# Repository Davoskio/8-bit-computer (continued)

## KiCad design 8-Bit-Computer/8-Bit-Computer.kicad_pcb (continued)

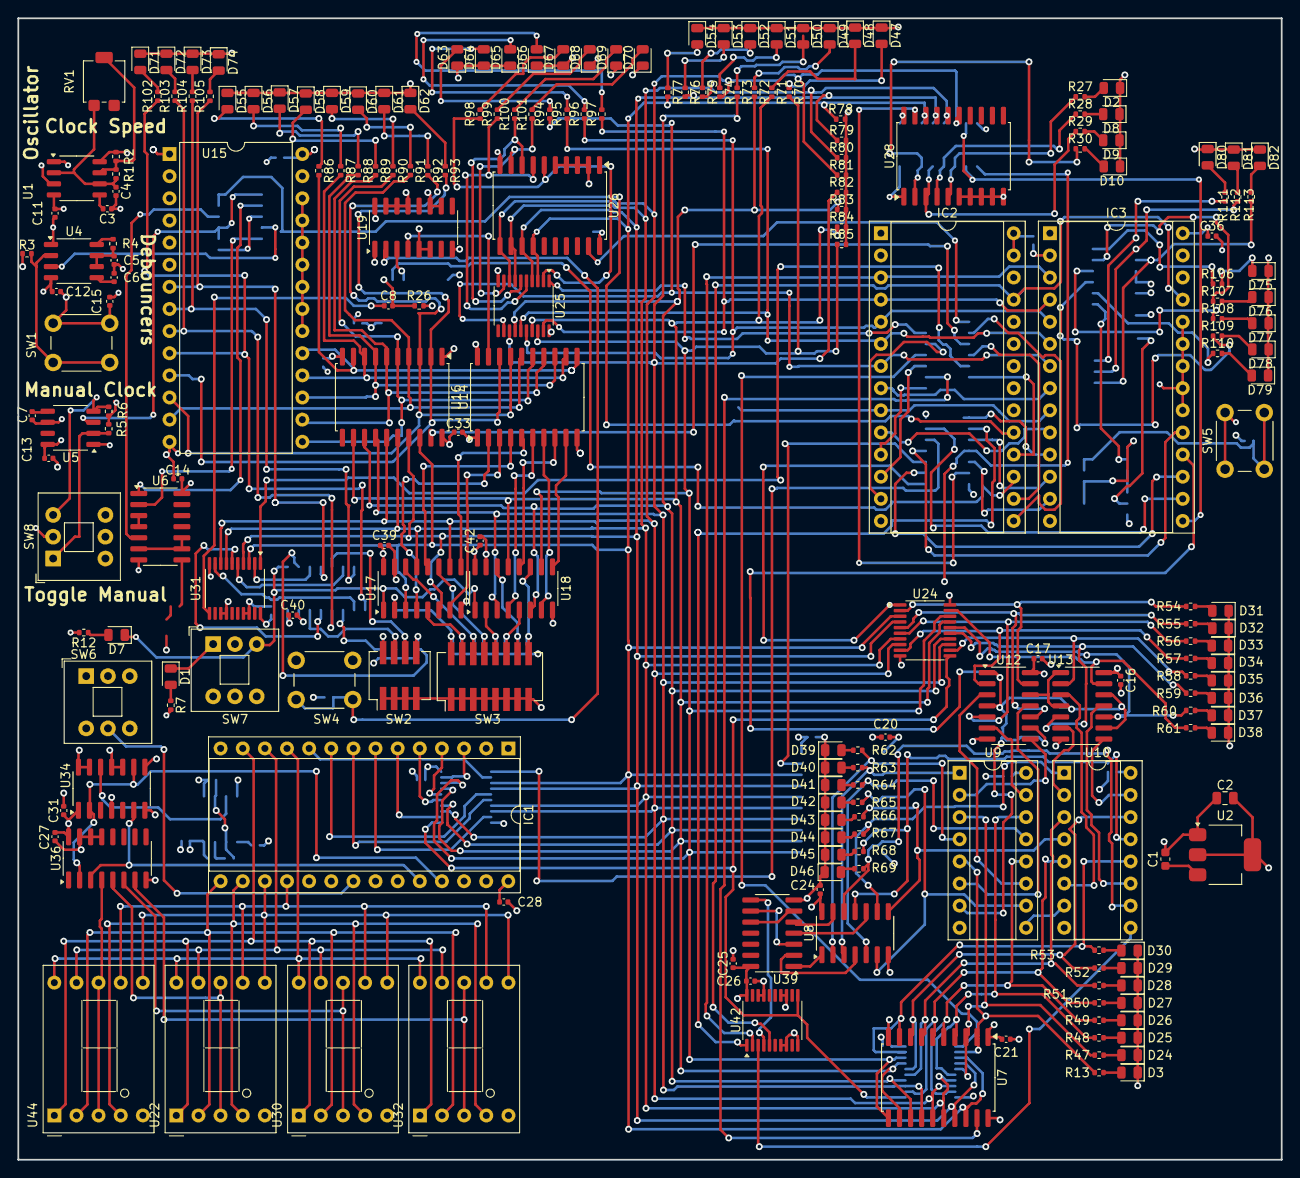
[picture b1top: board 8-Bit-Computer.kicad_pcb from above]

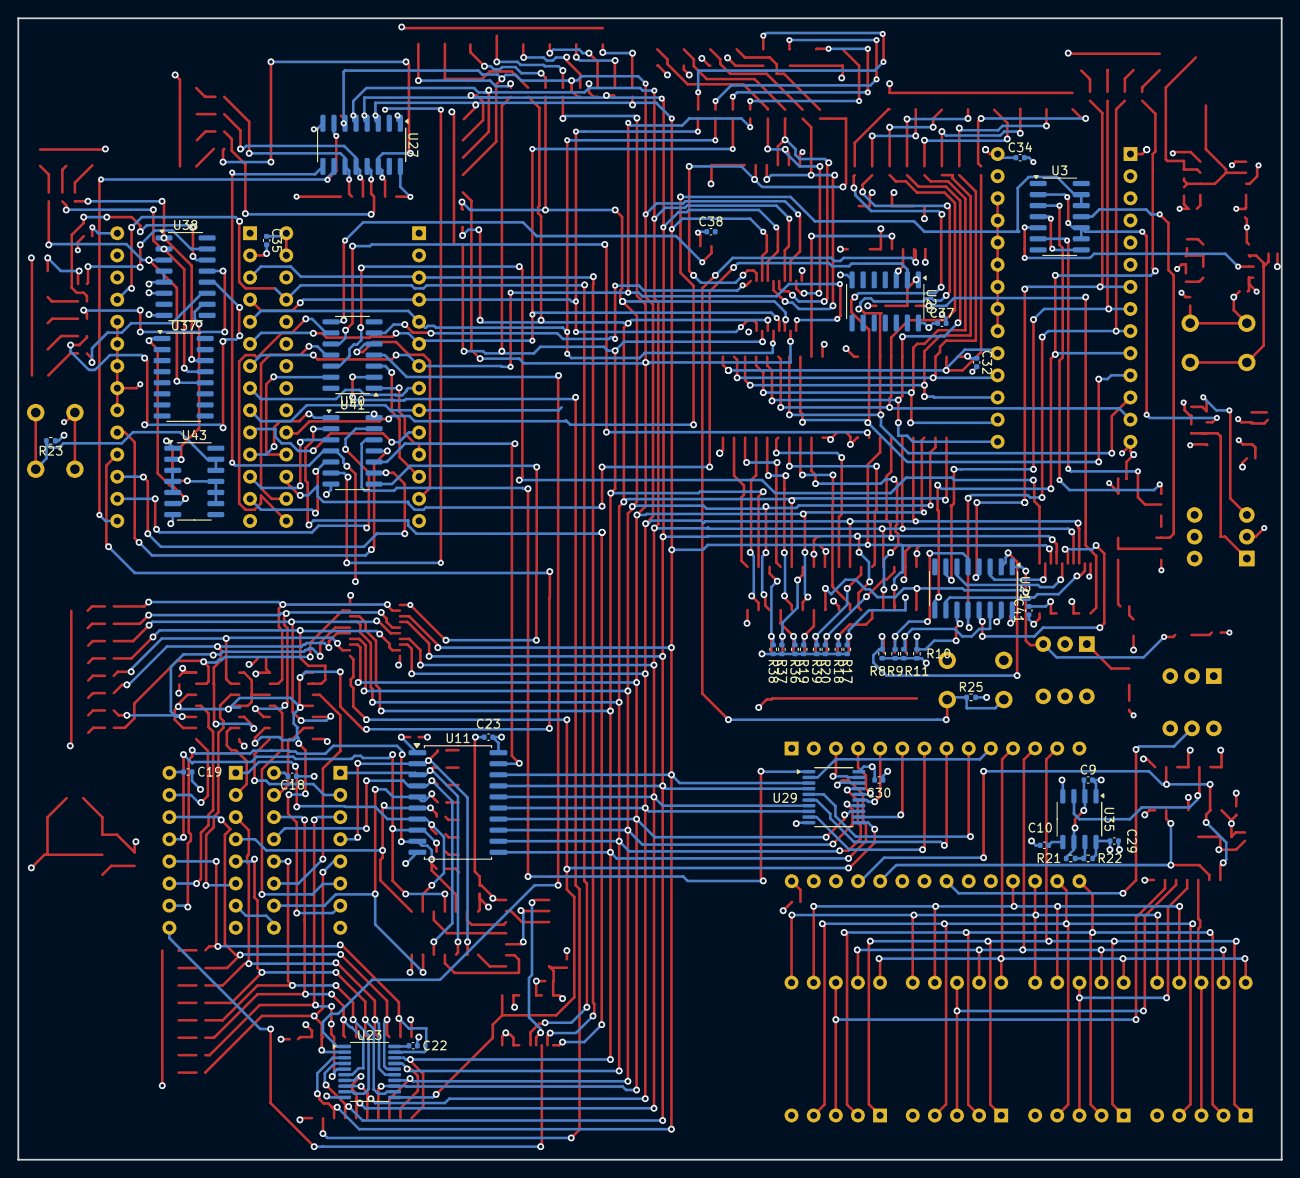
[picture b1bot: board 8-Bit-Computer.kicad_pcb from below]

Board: 4 copper layers, 145.0 x 131.0 mm, 260 parts (43 on the bottom side), 261 nets.

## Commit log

2023-12-29 first-commit
2023-12-29 Added a file, to make sure I can commit
2023-12-29 Added KiCAD project for 8 bit computer
2023-12-29 Added project status file
2023-12-29 status
2023-12-29 went to sleep
2023-12-29 status changed
2023-12-29 finished monostable
2023-12-30 working rn
2023-12-30 finished clock module
2023-12-30 working registers
2023-12-30 working on alu
2023-12-31 finishing alu
2023-12-31 ALU done
2024-01-02 starting RAM module
2024-01-02 not done much
2024-01-03 continuing memory
2024-01-03 needed to go somewhere
2024-01-03 still working on mem
2024-01-04 working on mem
2024-01-04 mem done. will review tomorrow.
2024-01-04 changed register chips to 74ls377
2024-01-04 working on pc and instruction reg
2024-01-04 will be back at it
2024-01-06 working now
2024-01-06 gbti
2024-01-10 I wonder what EEPROM chip to use
2024-04-04 will add eeprom schematic
2024-04-06 added eeprom and 7-seg display
2024-04-06 edited project-status.txt file
2024-04-17 Updated Project Status File Dominic
2024-04-17 Cleaned up Current Schematics
2024-04-17 updated status file
2024-04-19 Cleaned up RAM module
2024-04-20 completed ALU and most of the control logic
2024-04-20 Completed Schematics Version 1
2024-04-21 Finished adding footprints
2024-04-22 finished the PCB layout for ALU and clock
2024-04-22 completed display
2024-04-25 Finished Ram and started control logic
2024-04-28 remaining to fit in clock
2024-04-30 need to place leds
2024-05-02 done with all LEDs except control word
2024-05-03 fixing errors
2024-05-07 removed control word LEDs
2024-05-20 component outline collision and via clearance
2024-05-21 fixed a few via placements
2024-05-23 no more errors or warnings
2024-05-25 no more warnings or errors
2024-05-28 backups
2024-05-28 Created Gerber Files
2024-05-30 added R and C values
2024-06-01 changed some capacitors and resistors to top side
2024-11-25 schematic and PCB pics
